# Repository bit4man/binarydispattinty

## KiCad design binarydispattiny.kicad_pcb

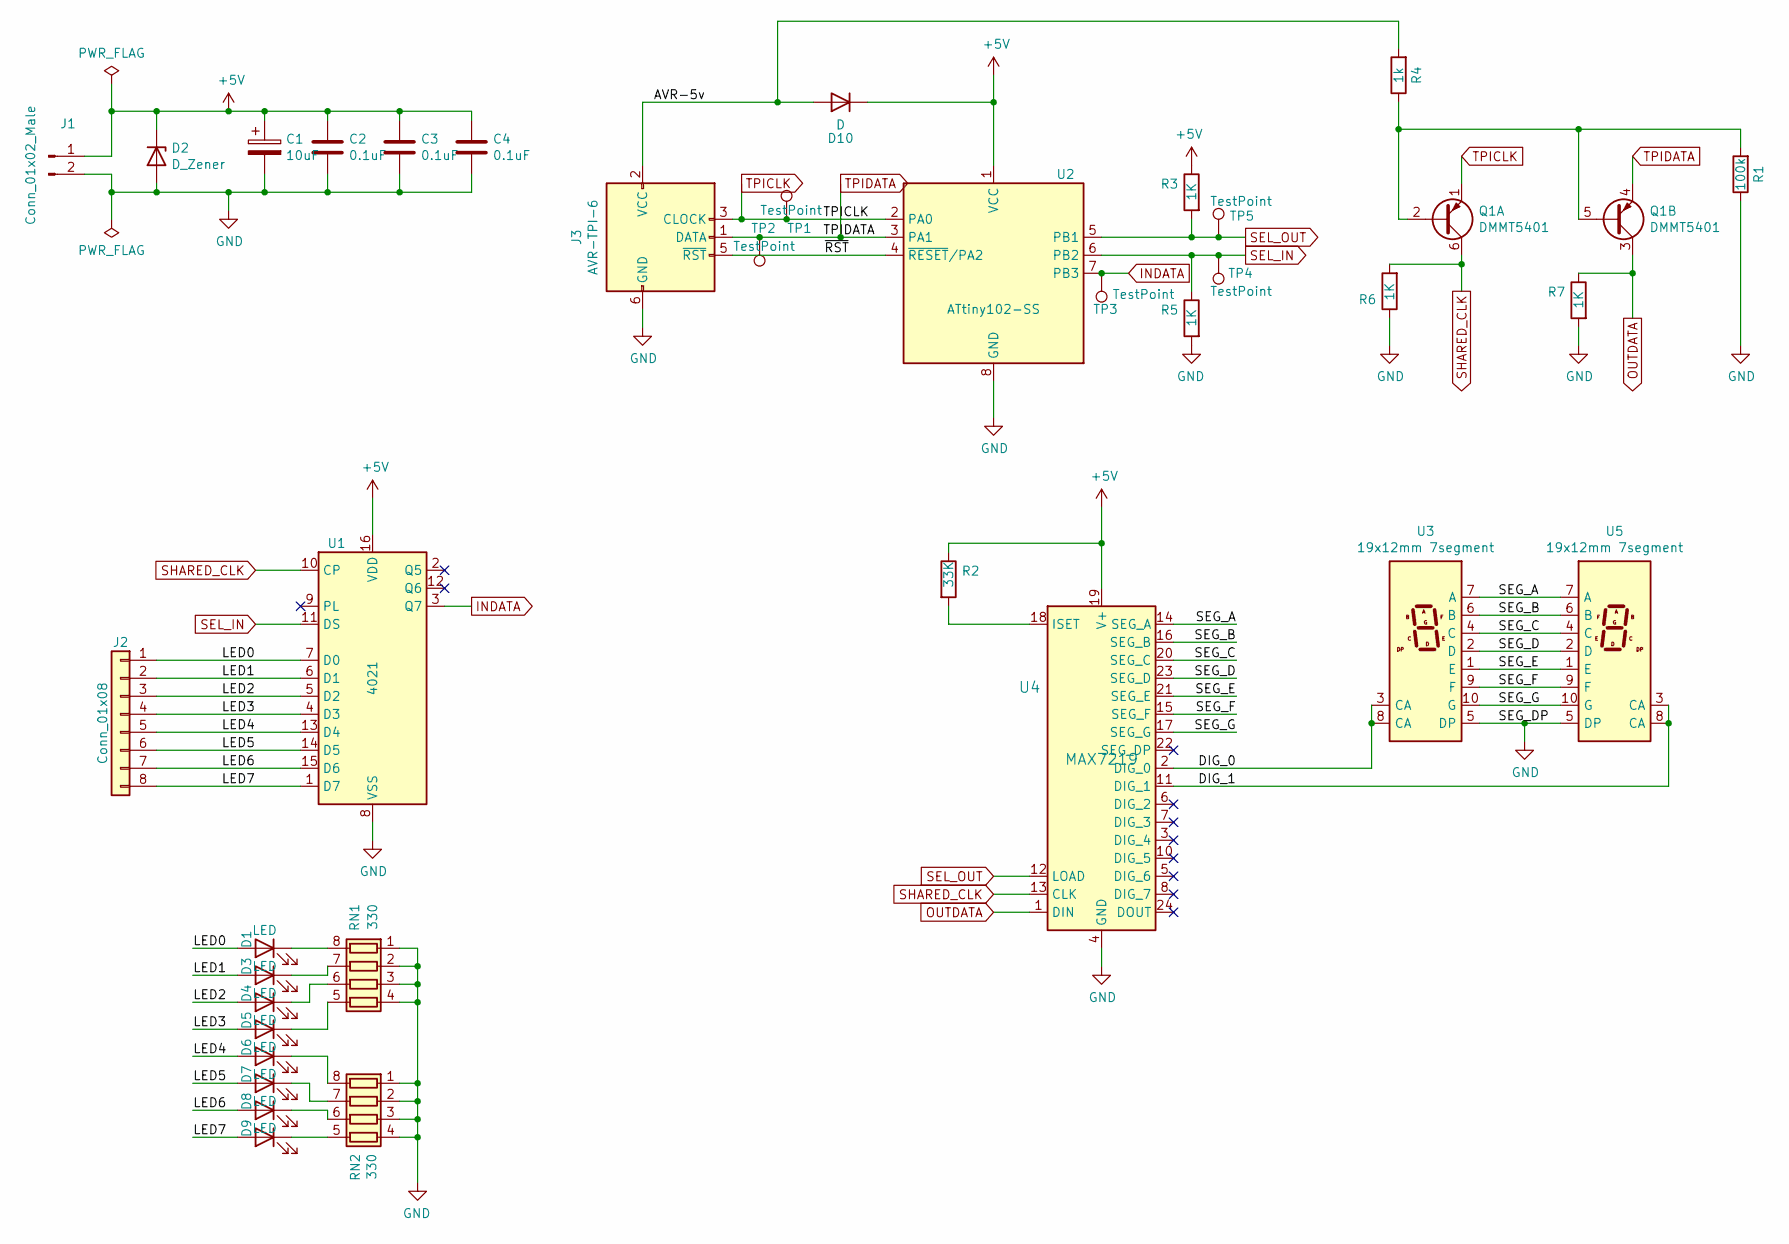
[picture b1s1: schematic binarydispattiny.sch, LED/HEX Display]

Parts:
C1: 10uF; CP_Elec_5x5.4
C2, C3, C4: 0.1uF; C_1206_3216Metric_Pad1.42x1.75mm_HandSolder
D1, D3, D4, D5, D6, D7, D8, D9: LED; LED_1206_3216Metric_Pad1.42x1.75mm_HandSolder
D2: D_Zener; D_1206_3216Metric_Pad1.42x1.75mm_HandSolder
D10: D; D_1206_3216Metric
J1: Conn_01x02_Male; PinHeader_1x02_P2.54mm_Vertical
J2: Conn_01x08; PinHeader_1x08_P2.54mm_Horizontal
J3: AVR-TPI-6; IDC-Header_2x03_P2.54mm_Vertical
Q1: DMMT5401; SOT-23-6_Handsoldering
R1: 100k; R_1206_3216Metric_Pad1.42x1.75mm_HandSolder
R2: 33K; R_1206_3216Metric_Pad1.42x1.75mm_HandSolder
R3, R5, R6, R7: 1K; R_1206_3216Metric_Pad1.42x1.75mm_HandSolder
R4: 1k; R_1206_3216Metric_Pad1.42x1.75mm_HandSolder
RN1, RN2: 330; R_Array_Convex_4x0603
TP1, TP2, TP3, TP4, TP5: TestPoint; TestPoint_Pad_1.0x1.0mm
U1: 4021; SOIC-16W_5.3x10.2mm_P1.27mm
U2: ATtiny102-SS; SOIC-8_3.9x4.9mm_P1.27mm
U3, U5: 19x12mm 7segment; 7SegmentLED_LTS6760_LTS6780
U4: MAX7219; SOP-24_7.5x15.4mm_P1.27mm

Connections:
+5V: C1.1, C2.1, C3.1, C4.1, D2.1 (K), D10.1 (K), J1.1, R2.1, R3.1, U1.16 (VDD), U2.1 (VCC), U4.19 (V+)
/AVR-5v: D10.2 (A), J3.2 (VCC), R4.2
/DIG_0: U3.3 (CA), U3.8 (CA), U4.2 (DIG_0)
/DIG_1: U4.11 (DIG_1), U5.3 (CA), U5.8 (CA)
/LED0: D1.2 (A), J2.1, U1.7 (D0)
/LED1: D3.2 (A), J2.2, U1.6 (D1)
/LED2: D4.2 (A), J2.3, U1.5 (D2)
/LED3: D5.2 (A), J2.4, U1.4 (D3)
/LED4: D6.2 (A), J2.5, U1.13 (D4)
/LED5: D7.2 (A), J2.6, U1.14 (D5)
/LED6: D8.2 (A), J2.7, U1.15 (D6)
/LED7: D9.2 (A), J2.8, U1.1 (D7)
/SEG_A: U3.7 (A), U4.14 (SEG_A), U5.7 (A)
/SEG_B: U3.6 (B), U4.16 (SEG_B), U5.6 (B)
/SEG_C: U3.4 (C), U4.20 (SEG_C), U5.4 (C)
/SEG_D: U3.2 (D), U4.23 (SEG_D), U5.2 (D)
/SEG_E: U3.1 (E), U4.21 (SEG_E), U5.1 (E)
/SEG_F: U3.9 (F), U4.15 (SEG_F), U5.9 (F)
/SEG_G: U3.10 (G), U4.17 (SEG_G), U5.10 (G)
/~RST: J3.5 (~RST), U2.4 (~RESET~/PA2)
GND: C1.2, C2.2, C3.2, C4.2, D2.2 (A), J1.2, J3.6 (GND), R1.1, R5.2, R6.1, R7.2, RN1.1 (R1.1), RN1.2 (R2.1), RN1.3 (R3.1), RN1.4 (R4.1), RN2.1 (R1.1), RN2.2 (R2.1), RN2.3 (R3.1), RN2.4 (R4.1), U1.8 (VSS), U2.8 (GND), U3.5 (DP), U4.4 (GND), U4.9 (GND), U5.5 (DP)
INDATA: TP3.1, U1.3 (Q7), U2.7 (PB3)
unnamed: D1.1 (K), RN1.8 (R1.2)
unnamed: D3.1 (K), RN1.7 (R2.2)
unnamed: D4.1 (K), RN1.6 (R3.2)
unnamed: D5.1 (K), RN1.5 (R4.2)
unnamed: D6.1 (K), RN2.8 (R1.2)
unnamed: D7.1 (K), RN2.7 (R2.2)
unnamed: D8.1 (K), RN2.6 (R3.2)
unnamed: D9.1 (K), RN2.5 (R4.2)
unnamed: Q1.2 (B1), Q1.5 (B2), R1.2, R4.1
unnamed: R2.2, U4.18 (ISET)
OUTDATA: Q1.3 (C2), R7.1, U4.1 (DIN)
SEL_IN: R5.1, TP4.1, U1.11 (DS), U2.6 (PB2)
SEL_OUT: R3.2, TP5.1, U2.5 (PB1), U4.12 (LOAD)
SHARED_CLK: Q1.6 (C1), R6.2, U1.10 (CP), U4.13 (CLK)
TPICLK: J3.3 (CLOCK), Q1.1 (E1), TP1.1, U2.2 (PA0)
TPIDATA: J3.1 (DATA), Q1.4 (E2), TP2.1, U2.3 (PA1)

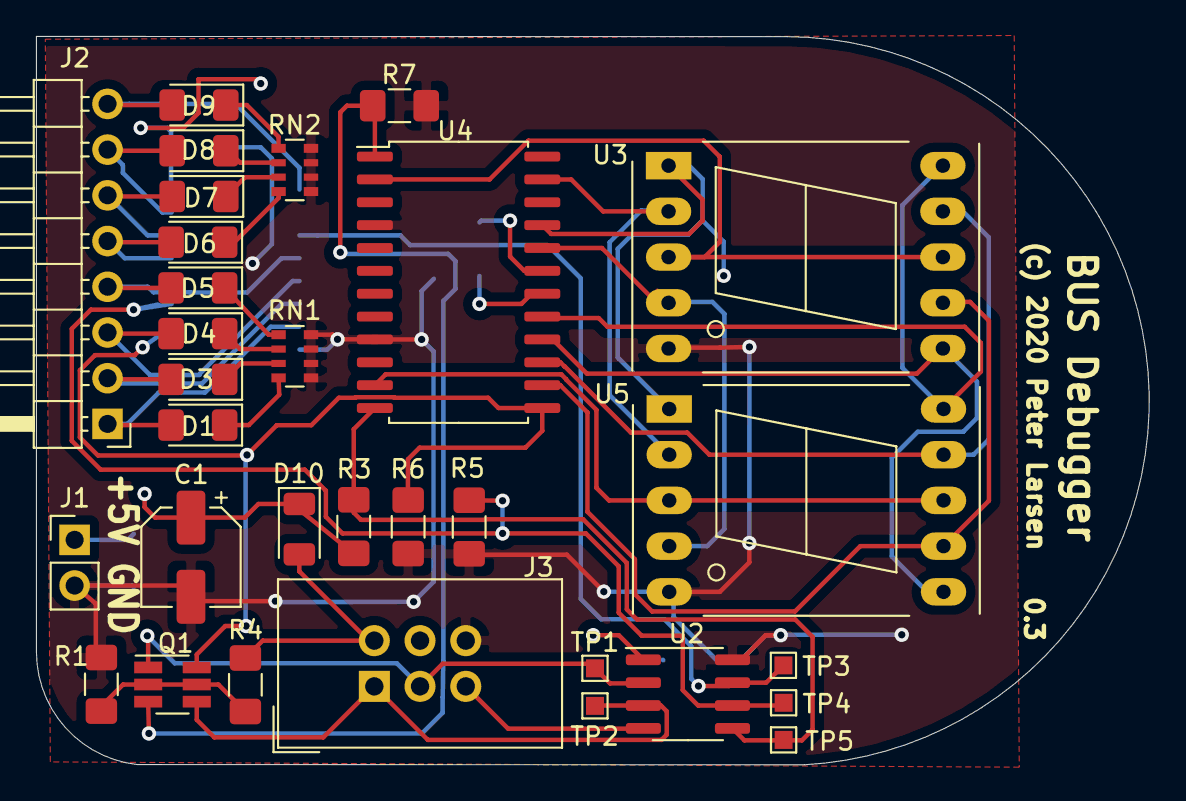
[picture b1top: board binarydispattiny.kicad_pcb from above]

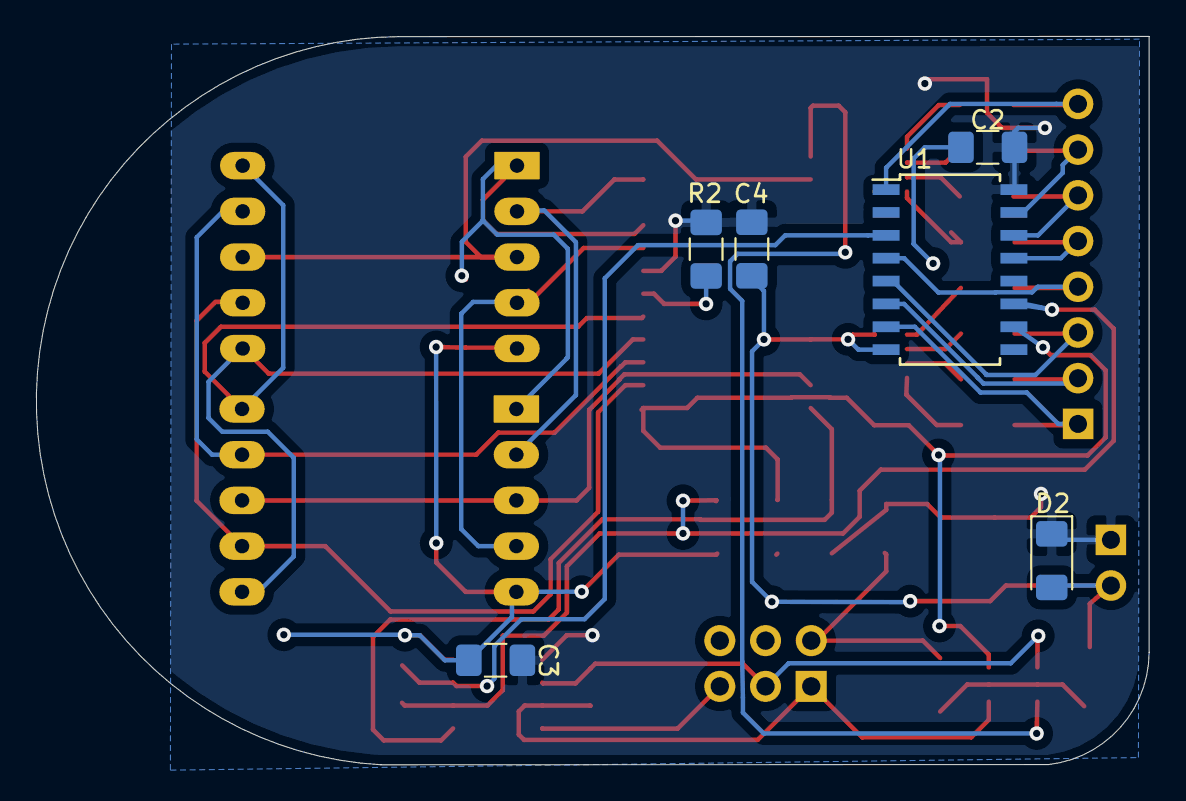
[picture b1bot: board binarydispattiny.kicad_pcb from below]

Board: 2 copper layers, 61.8 x 40.5 mm, 37 parts (6 on the bottom side), 38 nets.

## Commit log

2020-05-27 Create LICENSE
2020-05-27 Added 0.2 schematics
2020-05-27 Added license (again)
2020-06-02 Fixed MAX7912 sizing
2020-06-02 Fixed MAX7912 sizing #2
2020-06-02 Added test points
2020-06-02 Added Gerber Files

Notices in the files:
binarydispattiny.kicad_pcb:
(c) 2020 Peter Larsen
